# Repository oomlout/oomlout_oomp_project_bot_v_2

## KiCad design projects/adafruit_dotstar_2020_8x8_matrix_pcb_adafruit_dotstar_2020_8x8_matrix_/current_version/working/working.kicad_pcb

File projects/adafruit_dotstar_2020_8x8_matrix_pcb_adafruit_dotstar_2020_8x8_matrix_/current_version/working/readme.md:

# dotstar_2020_8x8_matrix_pcb
 
## summary 
* id: adafruit_dotstar_2020_8x8_matrix_pcb_adafruit_dotstar_2020_8x8_matrix_
* user: adafruit
* name: dotstar_2020_8x8_matrix_pcb
* board: adafruit_dotstar_2020_8x8_matrix_
* repo: https://github.com/adafruit/DotStar-2020-8x8-Matrix-PCB

* src_file_repo_sch: 
* src_file_repo_sch_link: https://github.com/adafruit/DotStar-2020-8x8-Matrix-PCB/tree/master/
* full details link: https://github.com/oomlout/oomlout_oomp_project_bot_v_2/tree/main/projects/adafruit_dotstar_2020_8x8_matrix_pcb_adafruit_dotstar_2020_8x8_matrix_/current_version/working  

## schematic  
  
[schematic (pdf)](working_schematic.pdf) 

## pcb  

[board (pdf)](working.pdf)  

## working_bom
| Id | Designator | Footprint | Quantity | Designation | Supplier and ref |  | None | 
| --- | --- | --- | --- | --- | --- | --- | --- | 
| 1 | LED61,LED15,LED52,LED5,LED2,LED56,LED29,LED42,LED31,LED59,LED53,LED34,LED33,LED37,LED30,LED3,LED13,LED58,LED16,LED47,LED54,LED48,LED6,LED27,LED62,LED21,LED20,LED49,LED10,LED8,LED32,LED22,LED45,LED55,LED40,LED23,LED36,LED35,LED4,LED26,LED7,LED18,LED43,LED12,LED19,LED60,LED63,LED9,LED11,LED46,LED50,LED28,LED38,LED41,LED17,LED39,LED51,LED64,LED24,LED44,LED57,LED14,LED1,LED25 | APA102_2020 | 64 |  |  |  | [''] | 
| 2 | @HOLE10,@HOLE0,@HOLE5,@HOLE3,@HOLE8,@HOLE2,@HOLE18,@HOLE16,@HOLE4,@HOLE6,@HOLE21,@HOLE11,@HOLE19,@HOLE9,@HOLE1,@HOLE15,@HOLE17,@HOLE12,@HOLE23,@HOLE22,@HOLE20,@HOLE13,@HOLE7,@HOLE14 |  | 24 |  |  |  | [''] | 
| 3 | FID2,FID3,FID1 | FIDUCIAL_0.5MM | 3 | FIDUCIAL_0.5MM |  |  | [''] | 
| 4 | CO0,V3,G3,V2,DI0,V1,G2,DO0,CI0,G1 | TP20R | 10 | TPTP20R |  |  | [''] | 
| 5 | U$1 | ADAFRUIT_TEXT_20MM | 1 |  |  |  | [''] | 

## bom_schematic
| Ref | Qnty | Value | Cmp name | Footprint | Description | Vendor | DNP | 
| --- | --- | --- | --- | --- | --- | --- | --- | 
| CI0 | 1 | TPTP20R | TPTP20R | working:TP20R |  |  |  | 
| CO0 | 1 | TPTP20R | TPTP20R | working:TP20R |  |  |  | 
| DI0 | 1 | TPTP20R | TPTP20R | working:TP20R |  |  |  | 
| DO0 | 1 | TPTP20R | TPTP20R | working:TP20R |  |  |  | 
| FID1, FID2, FID3 | 3 | FIDUCIAL_0.5MM | FIDUCIAL_0.5MM | working:FIDUCIAL_0.5MM |  |  |  | 
| G1, G2, G3 | 3 | TPTP20R | TPTP20R | working:TP20R |  |  |  | 
| LED1, LED2, LED3, LED4, LED5, LED6, LED7, LED8, LED9, LED10, LED11, LED12, LED13, LED14, LED15, LED16, LED17, LED18, LED19, LED20, LED21, LED22, LED23, LED24, LED25, LED26, LED27, LED28, LED29, LED30, LED31, LED32, LED33, LED34, LED35, LED36, LED37, LED38, LED39, LED40, LED41, LED42, LED43, LED44, LED45, LED46, LED47, LED48, LED49, LED50, LED51, LED52, LED53, LED54, LED55, LED56, LED57, LED58, LED59, LED60, LED61, LED62, LED63, LED64 | 64 | APA1022020 | APA1022020 | working:APA102_2020 |  |  |  | 
| V1, V2, V3 | 3 | TPTP20R | TPTP20R | working:TP20R |  |  |  |

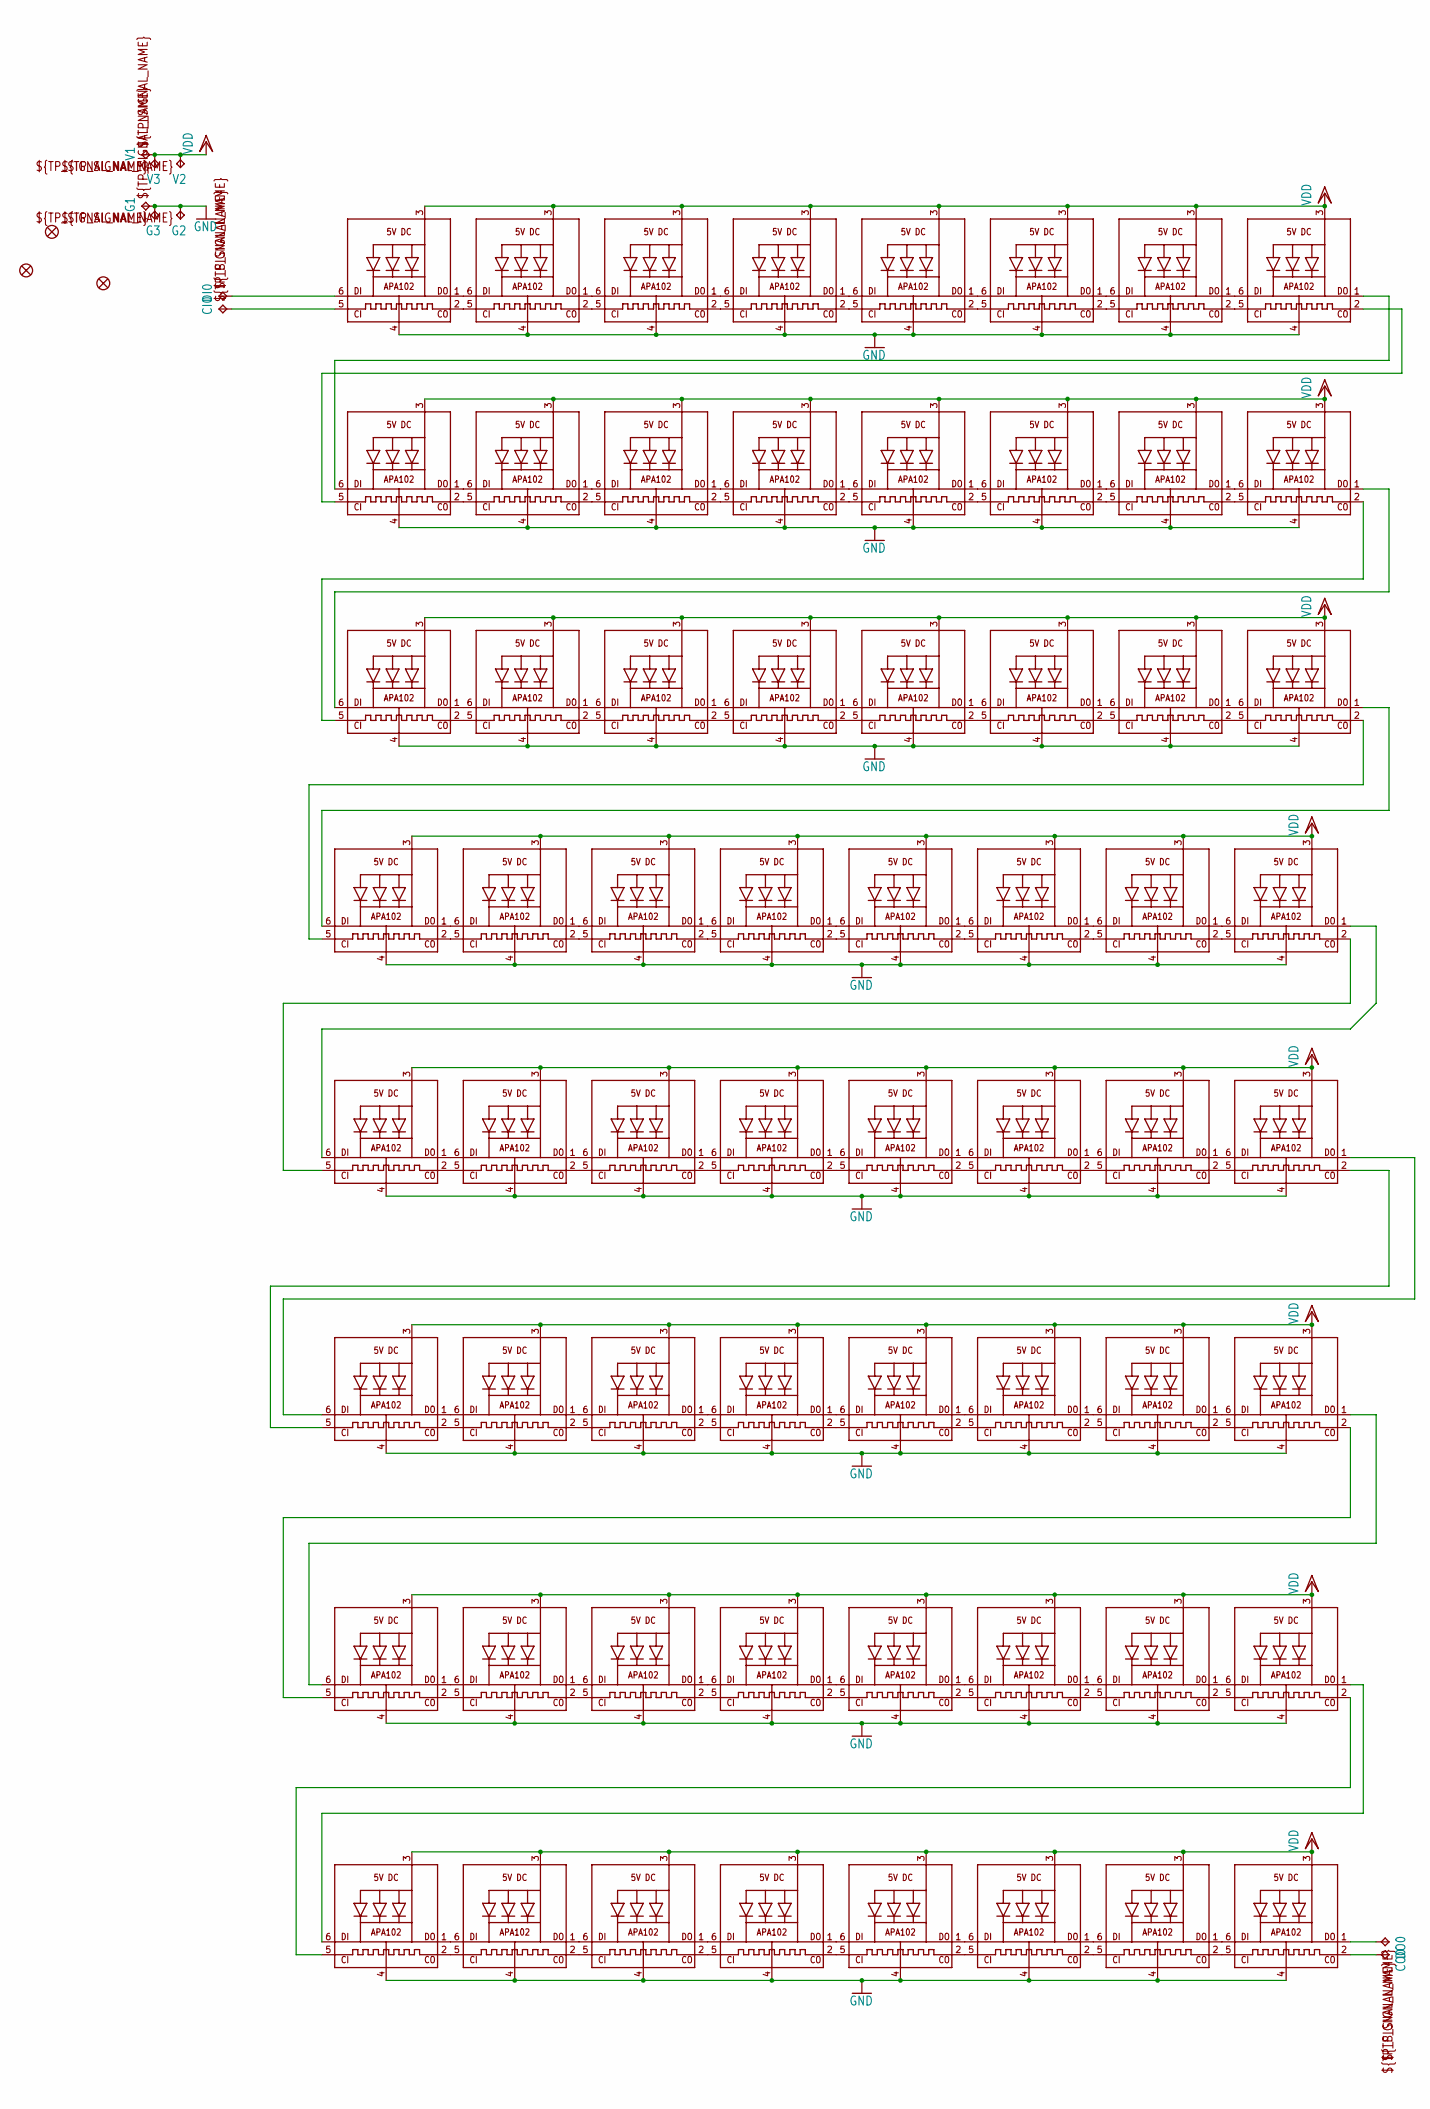
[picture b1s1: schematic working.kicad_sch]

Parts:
CI0: TPTP20R; TP20R
CO0: TPTP20R; TP20R
DI0: TPTP20R; TP20R
DO0: TPTP20R; TP20R
FID1, FID2, FID3: FIDUCIAL_0.5MM
G1, G2, G3: TPTP20R; TP20R
LED1, LED2, LED3, LED4, LED5, LED6, LED7, LED8, LED9, LED10, LED11, LED12, LED13, LED14, LED15, LED16, LED17, LED18, LED19, LED20, LED21, LED22, LED23, LED24, LED25, LED26, LED27, LED28, LED29, LED30, LED31, LED32, LED33, LED34, LED35, LED36, LED37, LED38, LED39, LED40, LED41, LED42, LED43, LED44, LED45, LED46, LED47, LED48, LED49, LED50, LED51, LED52, LED53, LED54, LED55, LED56, LED57, LED58, LED59, LED60, LED61, LED62, LED63, LED64: APA1022020; APA102_2020
V1, V2, V3: TPTP20R; TP20R

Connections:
C0: CO0.TP, LED64.2 (CKO)
CIN: CI0.TP, LED1.5 (CKI)
D0: DO0.TP, LED64.1 (DO)
DIN: DI0.TP, LED1.6 (DI)
GND: G1.TP, G2.TP, G3.TP, LED1.4 (GND), LED2.4 (GND), LED3.4 (GND), LED4.4 (GND), LED5.4 (GND), LED6.4 (GND), LED7.4 (GND), LED8.4 (GND), LED9.4 (GND), LED10.4 (GND), LED11.4 (GND), LED12.4 (GND), LED13.4 (GND), LED14.4 (GND), LED15.4 (GND), LED16.4 (GND), LED17.4 (GND), LED18.4 (GND), LED19.4 (GND), LED20.4 (GND), LED21.4 (GND), LED22.4 (GND), LED23.4 (GND), LED24.4 (GND), LED25.4 (GND), LED26.4 (GND), LED27.4 (GND), LED28.4 (GND), LED29.4 (GND), LED30.4 (GND), LED31.4 (GND), LED32.4 (GND), LED33.4 (GND), LED34.4 (GND), LED35.4 (GND), LED36.4 (GND), LED37.4 (GND), LED38.4 (GND), LED39.4 (GND), LED40.4 (GND), LED41.4 (GND), LED42.4 (GND), LED43.4 (GND), LED44.4 (GND), LED45.4 (GND), LED46.4 (GND), LED47.4 (GND), LED48.4 (GND), LED49.4 (GND), LED50.4 (GND), LED51.4 (GND), LED52.4 (GND), LED53.4 (GND), LED54.4 (GND), LED55.4 (GND), LED56.4 (GND), LED57.4 (GND), LED58.4 (GND), LED59.4 (GND), LED60.4 (GND), LED61.4 (GND), LED62.4 (GND), LED63.4 (GND), LED64.4 (GND)
unnamed: LED1.1 (DO), LED2.6 (DI)
unnamed: LED1.2 (CKO), LED2.5 (CKI)
unnamed: LED2.1 (DO), LED3.6 (DI)
unnamed: LED2.2 (CKO), LED3.5 (CKI)
unnamed: LED3.1 (DO), LED4.6 (DI)
unnamed: LED3.2 (CKO), LED4.5 (CKI)
unnamed: LED4.1 (DO), LED5.6 (DI)
unnamed: LED4.2 (CKO), LED5.5 (CKI)
unnamed: LED5.1 (DO), LED6.6 (DI)
unnamed: LED5.2 (CKO), LED6.5 (CKI)
unnamed: LED6.1 (DO), LED7.6 (DI)
unnamed: LED6.2 (CKO), LED7.5 (CKI)
unnamed: LED7.1 (DO), LED8.6 (DI)
unnamed: LED7.2 (CKO), LED8.5 (CKI)
unnamed: LED9.1 (DO), LED10.6 (DI)
unnamed: LED9.2 (CKO), LED10.5 (CKI)
unnamed: LED10.1 (DO), LED11.6 (DI)
unnamed: LED10.2 (CKO), LED11.5 (CKI)
unnamed: LED11.1 (DO), LED12.6 (DI)
unnamed: LED11.2 (CKO), LED12.5 (CKI)
unnamed: LED12.1 (DO), LED13.6 (DI)
unnamed: LED12.2 (CKO), LED13.5 (CKI)
unnamed: LED13.1 (DO), LED14.6 (DI)
unnamed: LED13.2 (CKO), LED14.5 (CKI)
unnamed: LED14.1 (DO), LED15.6 (DI)
unnamed: LED14.2 (CKO), LED15.5 (CKI)
unnamed: LED15.1 (DO), LED16.6 (DI)
unnamed: LED15.2 (CKO), LED16.5 (CKI)
unnamed: LED17.1 (DO), LED18.6 (DI)
unnamed: LED17.2 (CKO), LED18.5 (CKI)
unnamed: LED18.1 (DO), LED19.6 (DI)
unnamed: LED18.2 (CKO), LED19.5 (CKI)
unnamed: LED19.1 (DO), LED20.6 (DI)
unnamed: LED19.2 (CKO), LED20.5 (CKI)
unnamed: LED20.1 (DO), LED21.6 (DI)
unnamed: LED20.2 (CKO), LED21.5 (CKI)
unnamed: LED21.1 (DO), LED22.6 (DI)
unnamed: LED21.2 (CKO), LED22.5 (CKI)
unnamed: LED22.1 (DO), LED23.6 (DI)
unnamed: LED22.2 (CKO), LED23.5 (CKI)
unnamed: LED23.1 (DO), LED24.6 (DI)
unnamed: LED23.2 (CKO), LED24.5 (CKI)
unnamed: LED25.1 (DO), LED26.6 (DI)
unnamed: LED25.2 (CKO), LED26.5 (CKI)
unnamed: LED26.1 (DO), LED27.6 (DI)
unnamed: LED26.2 (CKO), LED27.5 (CKI)
unnamed: LED27.1 (DO), LED28.6 (DI)
unnamed: LED27.2 (CKO), LED28.5 (CKI)
unnamed: LED28.1 (DO), LED29.6 (DI)
unnamed: LED28.2 (CKO), LED29.5 (CKI)
unnamed: LED29.1 (DO), LED30.6 (DI)
unnamed: LED29.2 (CKO), LED30.5 (CKI)
unnamed: LED30.1 (DO), LED31.6 (DI)
unnamed: LED30.2 (CKO), LED31.5 (CKI)
unnamed: LED31.1 (DO), LED32.6 (DI)
unnamed: LED31.2 (CKO), LED32.5 (CKI)
unnamed: LED33.1 (DO), LED34.6 (DI)
unnamed: LED33.2 (CKO), LED34.5 (CKI)
unnamed: LED34.1 (DO), LED35.6 (DI)
unnamed: LED34.2 (CKO), LED35.5 (CKI)
unnamed: LED35.1 (DO), LED36.6 (DI)
unnamed: LED35.2 (CKO), LED36.5 (CKI)
unnamed: LED36.1 (DO), LED37.6 (DI)
unnamed: LED36.2 (CKO), LED37.5 (CKI)
unnamed: LED37.1 (DO), LED38.6 (DI)
unnamed: LED37.2 (CKO), LED38.5 (CKI)
unnamed: LED38.1 (DO), LED39.6 (DI)
unnamed: LED38.2 (CKO), LED39.5 (CKI)
unnamed: LED39.1 (DO), LED40.6 (DI)
unnamed: LED39.2 (CKO), LED40.5 (CKI)
unnamed: LED41.1 (DO), LED42.6 (DI)
unnamed: LED41.2 (CKO), LED42.5 (CKI)
unnamed: LED42.1 (DO), LED43.6 (DI)
unnamed: LED42.2 (CKO), LED43.5 (CKI)
unnamed: LED43.1 (DO), LED44.6 (DI)
unnamed: LED43.2 (CKO), LED44.5 (CKI)
unnamed: LED44.1 (DO), LED45.6 (DI)
unnamed: LED44.2 (CKO), LED45.5 (CKI)
unnamed: LED45.1 (DO), LED46.6 (DI)
unnamed: LED45.2 (CKO), LED46.5 (CKI)
unnamed: LED46.1 (DO), LED47.6 (DI)
unnamed: LED46.2 (CKO), LED47.5 (CKI)
unnamed: LED47.1 (DO), LED48.6 (DI)
unnamed: LED47.2 (CKO), LED48.5 (CKI)
unnamed: LED49.1 (DO), LED50.6 (DI)
unnamed: LED49.2 (CKO), LED50.5 (CKI)
unnamed: LED50.1 (DO), LED51.6 (DI)
unnamed: LED50.2 (CKO), LED51.5 (CKI)
unnamed: LED51.1 (DO), LED52.6 (DI)
unnamed: LED51.2 (CKO), LED52.5 (CKI)
unnamed: LED52.1 (DO), LED53.6 (DI)
unnamed: LED52.2 (CKO), LED53.5 (CKI)
unnamed: LED53.1 (DO), LED54.6 (DI)
unnamed: LED53.2 (CKO), LED54.5 (CKI)
unnamed: LED54.1 (DO), LED55.6 (DI)
unnamed: LED54.2 (CKO), LED55.5 (CKI)
unnamed: LED55.1 (DO), LED56.6 (DI)
unnamed: LED55.2 (CKO), LED56.5 (CKI)
unnamed: LED57.1 (DO), LED58.6 (DI)
unnamed: LED57.2 (CKO), LED58.5 (CKI)
unnamed: LED58.1 (DO), LED59.6 (DI)
unnamed: LED58.2 (CKO), LED59.5 (CKI)
unnamed: LED59.1 (DO), LED60.6 (DI)
unnamed: LED59.2 (CKO), LED60.5 (CKI)
unnamed: LED60.1 (DO), LED61.6 (DI)
unnamed: LED60.2 (CKO), LED61.5 (CKI)
unnamed: LED61.1 (DO), LED62.6 (DI)
unnamed: LED61.2 (CKO), LED62.5 (CKI)
unnamed: LED62.1 (DO), LED63.6 (DI)
unnamed: LED62.2 (CKO), LED63.5 (CKI)
unnamed: LED63.1 (DO), LED64.6 (DI)
unnamed: LED63.2 (CKO), LED64.5 (CKI)
unnamed: LED8.1 (DO), LED9.6 (DI)
unnamed: LED8.2 (CKO), LED9.5 (CKI)
unnamed: LED16.1 (DO), LED17.6 (DI)
unnamed: LED16.2 (CKO), LED17.5 (CKI)
unnamed: LED24.1 (DO), LED25.6 (DI)
unnamed: LED24.2 (CKO), LED25.5 (CKI)
unnamed: LED32.1 (DO), LED33.6 (DI)
unnamed: LED32.2 (CKO), LED33.5 (CKI)
unnamed: LED56.1 (DO), LED57.6 (DI)
unnamed: LED56.2 (CKO), LED57.5 (CKI)
unnamed: LED48.2 (CKO), LED49.5 (CKI)
unnamed: LED48.1 (DO), LED49.6 (DI)
unnamed: LED40.2 (CKO), LED41.5 (CKI)
unnamed: LED40.1 (DO), LED41.6 (DI)
VDD: LED1.3 (VDD), LED2.3 (VDD), LED3.3 (VDD), LED4.3 (VDD), LED5.3 (VDD), LED6.3 (VDD), LED7.3 (VDD), LED8.3 (VDD), LED9.3 (VDD), LED10.3 (VDD), LED11.3 (VDD), LED12.3 (VDD), LED13.3 (VDD), LED14.3 (VDD), LED15.3 (VDD), LED16.3 (VDD), LED17.3 (VDD), LED18.3 (VDD), LED19.3 (VDD), LED20.3 (VDD), LED21.3 (VDD), LED22.3 (VDD), LED23.3 (VDD), LED24.3 (VDD), LED25.3 (VDD), LED26.3 (VDD), LED27.3 (VDD), LED28.3 (VDD), LED29.3 (VDD), LED30.3 (VDD), LED31.3 (VDD), LED32.3 (VDD), LED33.3 (VDD), LED34.3 (VDD), LED35.3 (VDD), LED36.3 (VDD), LED37.3 (VDD), LED38.3 (VDD), LED39.3 (VDD), LED40.3 (VDD), LED41.3 (VDD), LED42.3 (VDD), LED43.3 (VDD), LED44.3 (VDD), LED45.3 (VDD), LED46.3 (VDD), LED47.3 (VDD), LED48.3 (VDD), LED49.3 (VDD), LED50.3 (VDD), LED51.3 (VDD), LED52.3 (VDD), LED53.3 (VDD), LED54.3 (VDD), LED55.3 (VDD), LED56.3 (VDD), LED57.3 (VDD), LED58.3 (VDD), LED59.3 (VDD), LED60.3 (VDD), LED61.3 (VDD), LED62.3 (VDD), LED63.3 (VDD), LED64.3 (VDD), V1.TP, V2.TP, V3.TP

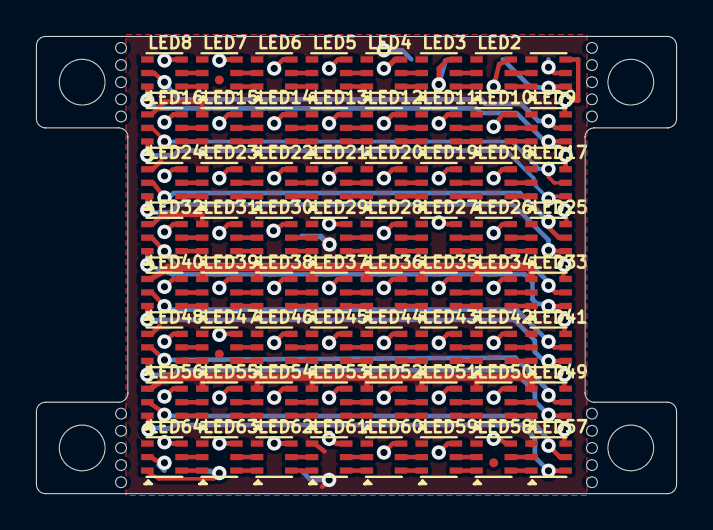
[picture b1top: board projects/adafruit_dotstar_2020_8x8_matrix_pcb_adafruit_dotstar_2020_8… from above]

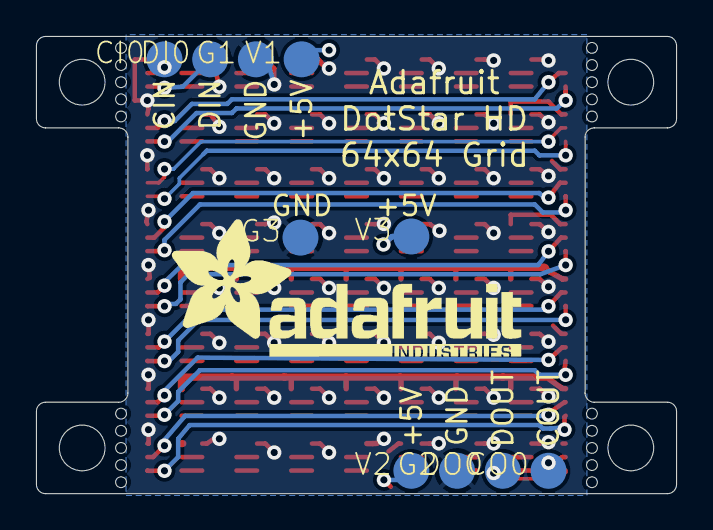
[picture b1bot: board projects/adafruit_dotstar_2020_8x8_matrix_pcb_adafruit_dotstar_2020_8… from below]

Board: 2 copper layers, 35.6 x 25.4 mm, 102 parts (11 on the bottom side), 132 nets.

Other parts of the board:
@HOLE0, @HOLE1, @HOLE2, @HOLE3, @HOLE4, @HOLE5, @HOLE6, @HOLE7, @HOLE8, @HOLE9, @HOLE10, @HOLE11, @HOLE12, @HOLE13, @HOLE14, @HOLE15, @HOLE16, @HOLE17, @HOLE18, @HOLE19, @HOLE20, @HOLE21, @HOLE22, @HOLE23: (no value)
U$1: ADAFRUIT_TEXT_20MM

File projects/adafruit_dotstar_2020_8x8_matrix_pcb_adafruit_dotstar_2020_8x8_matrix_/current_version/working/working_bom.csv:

"Id";"Designator";"Footprint";"Quantity";"Designation";"Supplier and ref";
1;"LED61,LED15,LED52,LED5,LED2,LED56,LED29,LED42,LED31,LED59,LED53,LED34,LED33,LED37,LED30,LED3,LED13,LED58,LED16,LED47,LED54,LED48,LED6,LED27,LED62,LED21,LED20,LED49,LED10,LED8,LED32,LED22,LED45,LED55,LED40,LED23,LED36,LED35,LED4,LED26,LED7,LED18,LED43,LED12,LED19,LED60,LED63,LED9,LED11,LED46,LED50,LED28,LED38,LED41,LED17,LED39,LED51,LED64,LED24,LED44,LED57,LED14,LED1,LED25";"APA102_2020";64;"";;;
2;"@HOLE10,@HOLE0,@HOLE5,@HOLE3,@HOLE8,@HOLE2,@HOLE18,@HOLE16,@HOLE4,@HOLE6,@HOLE21,@HOLE11,@HOLE19,@HOLE9,@HOLE1,@HOLE15,@HOLE17,@HOLE12,@HOLE23,@HOLE22,@HOLE20,@HOLE13,@HOLE7,@HOLE14";"";24;"";;;
3;"FID2,FID3,FID1";"FIDUCIAL_0.5MM";3;"FIDUCIAL_0.5MM";;;
4;"CO0,V3,G3,V2,DI0,V1,G2,DO0,CI0,G1";"TP20R";10;"TPTP20R";;;
5;"U$1";"ADAFRUIT_TEXT_20MM";1;"";;;

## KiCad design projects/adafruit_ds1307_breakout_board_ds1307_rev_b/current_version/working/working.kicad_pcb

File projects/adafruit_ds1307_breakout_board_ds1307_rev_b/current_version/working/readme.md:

# ds1307_breakout_board
 
## summary 
* id: adafruit_ds1307_breakout_board_ds1307_rev_b
* user: adafruit
* name: ds1307_breakout_board
* board: ds1307_rev_b
* repo: https://github.com/adafruit/DS1307-breakout-board

* src_file_repo_sch: 
* src_file_repo_sch_link: https://github.com/adafruit/DS1307-breakout-board/tree/master/
* full details link: https://github.com/oomlout/oomlout_oomp_project_bot_v_2/tree/main/projects/adafruit_ds1307_breakout_board_ds1307_rev_b/current_version/working  

## schematic  
  
[schematic (pdf)](working_schematic.pdf) 

## pcb  

[board (pdf)](working.pdf)  

## working_bom
| Id | Designator | Footprint | Quantity | Designation | Supplier and ref |  | None | 
| --- | --- | --- | --- | --- | --- | --- | --- | 
| 1 | U$1,U$4 | MOUNTINGHOLE_2.0_PLATED | 2 | MOUNTINGHOLE2.0 |  |  | [''] | 
| 2 | U1 | SOIC8_150MIL | 1 | DS1307 |  |  | [''] | 
| 3 | Q1 | CRYSTAL_8X3.8 | 1 | 32.768 |  |  | [''] | 
| 4 | R2,R1 | 0805-NO | 2 | 10K |  |  | [''] | 
| 5 | JP2 | 1X05_ROUND_76 | 1 |  |  |  | [''] | 
| 6 | FID1,FID2 | FIDUCIAL_1MM | 2 | FIDUCIAL" |  |  | [''] | 
| 7 | U$2 | ADAFRUIT_3.5MM | 1 |  |  |  | [''] | 
| 8 | C1 | 0805-NO | 1 | 0.1uF |  |  | [''] | 
| 9 | B1 | CR1220 | 1 | CR1220 |  |  | [''] | 
| 10 | SJ1,SJ2 | SOLDERJUMPER_CLOSEDWIRE | 2 |  |  |  | [''] | 
| 11 | U$3 | PCBFEAT-REV-040 | 1 |  |  |  | [''] | 
| 12 | U$5 | ADAFRUIT_5MM | 1 |  |  |  | [''] | 

## bom_schematic
| Ref | Qnty | Value | Cmp name | Footprint | Description | Vendor | DNP | 
| --- | --- | --- | --- | --- | --- | --- | --- | 
| B1 | 1 | CR1220 | BATTERYCR1220_SMT | working:CR1220 |  |  |  | 
| C1 | 1 | 0.1uF | CAP_CERAMIC0805-NOOUTLINE | working:0805-NO |  |  |  | 
| FID1, FID2 | 2 | FIDUCIAL"" | FIDUCIAL{dblquote}{dblquote} | working:FIDUCIAL_1MM |  |  |  | 
| JP2 | 1 | HEADER-1X576MIL | HEADER-1X576MIL | working:1X05_ROUND_76 |  |  |  | 
| Q1 | 1 | 32.768 | CRYSTAL8.0X3.8 | working:CRYSTAL_8X3.8 |  |  |  | 
| R1, R2 | 2 | 10K | RESISTOR0805_NOOUTLINE | working:0805-NO |  |  |  | 
| SJ1, SJ2 | 2 | SOLDERJUMPER_CLOSED | SOLDERJUMPER_CLOSED | working:SOLDERJUMPER_CLOSEDWIRE |  |  |  | 
| U1 | 1 | DS1307 | RTC_DS1307 | working:SOIC8_150MIL |  |  |  | 
| U$1, U$4 | 2 | MOUNTINGHOLE2.0 | MOUNTINGHOLE2.0 | working:MOUNTINGHOLE_2.0_PLATED |  |  |  | 

## mounting_holes
| x | y | package | value | ref | size | 
| --- | --- | --- | --- | --- | --- | 
| 0.0 | 20.32 | MOUNTINGHOLE_2.0_PLATED | MOUNTINGHOLE2.0 | U$1 | m3 | 
| 16.51 | 0.0 | MOUNTINGHOLE_2.0_PLATED | MOUNTINGHOLE2.0 | U$4 | m3 |

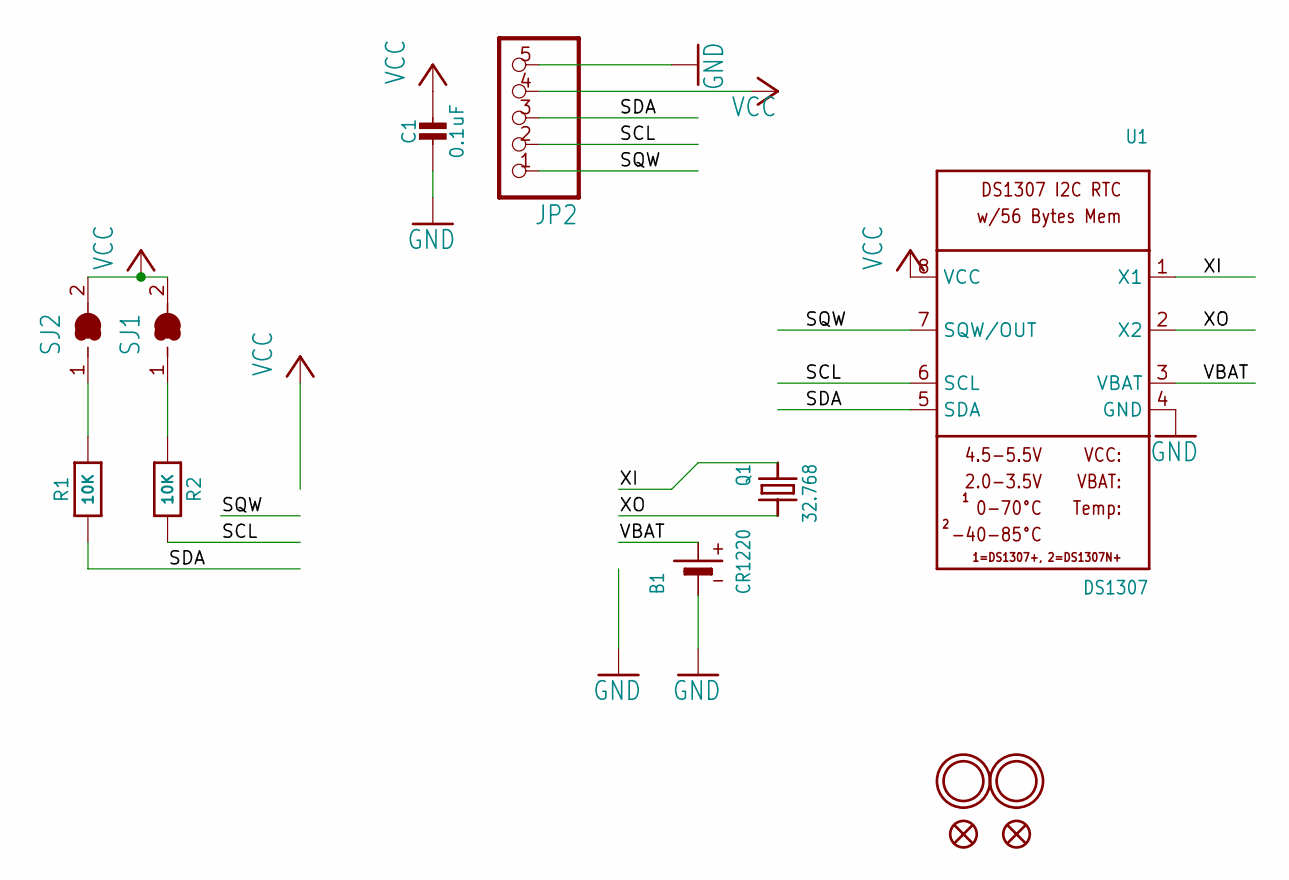
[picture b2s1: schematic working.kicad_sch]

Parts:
B1: CR1220
C1: 0.1uF; 0805-NO
FID1, FID2: FIDUCIAL""; FIDUCIAL_1MM
JP2: HEADER-1X576MIL; 1X05_ROUND_76
Q1: 32.768; CRYSTAL_8X3.8
R1, R2: 10K; 0805-NO
SJ1, SJ2: SOLDERJUMPER_CLOSED; SOLDERJUMPER_CLOSEDWIRE
U1: DS1307; SOIC8_150MIL
U$1, U$4: MOUNTINGHOLE2.0; MOUNTINGHOLE_2.0_PLATED

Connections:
GND: B1.-, C1.2, JP2.5, U1.4 (GND)
unnamed: R2.1, SJ1.1
unnamed: R1.2, SJ2.1
SCL: JP2.2, R2.2, U1.6 (SCL)
SDA: JP2.3, R1.1, U1.5 (SDA)
SQW: JP2.1, U1.7 (SQW/OUT)
VBAT: B1.+$1 (+), U1.3 (VBAT)
VCC: C1.1, JP2.4, SJ1.2, SJ2.2, U1.8 (VCC)
XI: Q1.P$1 (1), U1.1 (X1)
XO: Q1.P$4 (2), U1.2 (X2)

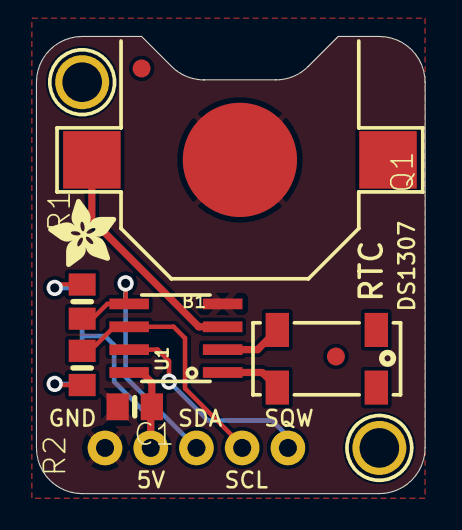
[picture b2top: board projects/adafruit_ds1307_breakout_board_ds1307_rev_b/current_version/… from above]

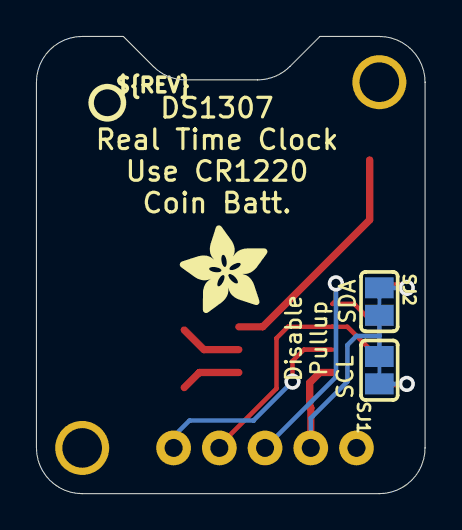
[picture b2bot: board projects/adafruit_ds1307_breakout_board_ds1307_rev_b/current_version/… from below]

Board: 16 copper layers, 21.6 x 25.4 mm, 16 parts (4 on the bottom side), 10 nets.

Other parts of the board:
U$2: ADAFRUIT_3.5MM
U$3: PCBFEAT-REV-040
U$5: ADAFRUIT_5MM

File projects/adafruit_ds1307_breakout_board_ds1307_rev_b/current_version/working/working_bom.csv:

"Id";"Designator";"Footprint";"Quantity";"Designation";"Supplier and ref";
1;"U$1,U$4";"MOUNTINGHOLE_2.0_PLATED";2;"MOUNTINGHOLE2.0";;;
2;"U1";"SOIC8_150MIL";1;"DS1307";;;
3;"Q1";"CRYSTAL_8X3.8";1;"32.768";;;
4;"R2,R1";"0805-NO";2;"10K";;;
5;"JP2";"1X05_ROUND_76";1;"";;;
6;"FID1,FID2";"FIDUCIAL_1MM";2;"FIDUCIAL""";;;
7;"U$2";"ADAFRUIT_3.5MM";1;"";;;
8;"C1";"0805-NO";1;"0.1uF";;;
9;"B1";"CR1220";1;"CR1220";;;
10;"SJ1,SJ2";"SOLDERJUMPER_CLOSEDWIRE";2;"";;;
11;"U$3";"PCBFEAT-REV-040";1;"";;;
12;"U$5";"ADAFRUIT_5MM";1;"";;;

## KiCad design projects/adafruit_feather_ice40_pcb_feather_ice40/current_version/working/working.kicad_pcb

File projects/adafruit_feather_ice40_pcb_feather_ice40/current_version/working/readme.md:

# feather_ice40_pcb
 
## summary 
* id: adafruit_feather_ice40_pcb_feather_ice40
* user: adafruit
* name: feather_ice40_pcb
* board: feather_ice40
* repo: https://github.com/adafruit/Feather-ICE40-PCB
* src_file_repo_kicad_pcb: feather_ice40.kicad_pcb
* src_file_repo_kicad_pcb_link: https://github.com/adafruit/Feather-ICE40-PCB/tree/master/feather_ice40.kicad_pcb

* src_file_repo_sch: feather_ice40.sch
* src_file_repo_sch_link: https://github.com/adafruit/Feather-ICE40-PCB/tree/master/feather_ice40.sch
* full details link: https://github.com/oomlout/oomlout_oomp_project_bot_v_2/tree/main/projects/adafruit_feather_ice40_pcb_feather_ice40/current_version/working  

## schematic  
  
[schematic (pdf)](working_schematic.pdf) 

## pcb  

[board (pdf)](working.pdf)  

## working_bom
| Id | Designator | Footprint | Quantity | Designation | Supplier and ref |  | None | 
| --- | --- | --- | --- | --- | --- | --- | --- | 
| 1 | U5 | QFN-32-1EP_5x5mm_Pitch0.5mm | 1 | SAMD21E |  |  | [''] | 
| 2 | D1 | D_SOD-123 | 1 | MBR120 |  |  | [''] | 
| 3 | J2 | JST_PH_S2B-PH-SM4-TB_02x2.00mm_Angled | 1 | CONN_01X02 |  |  | [''] | 
| 4 | J1 | Mini-USB-B-OshPark | 1 | USB_OTG |  |  | [''] | 
| 5 | J6,J5,J4,J3 | MountingHole_2.7mm_M2.5 | 4 | CONN_01X01 |  |  | [''] | 
| 6 | R8,R5,R10 | R_0603 | 3 | 1k |  |  | [''] | 
| 7 | R4 | R_0603 | 1 | 100k |  |  | [''] | 
| 8 | C20,C19,C16,C14,C6 | C_0603 | 5 | 10uF |  |  | [''] | 
| 9 | C18,C7 | C_0603 | 2 | 1uF |  |  | [''] | 
| 10 | D2 | D_0603 | 1 | Yellow |  |  | [''] | 
| 11 | D3 | D_0603 | 1 | Red |  |  | [''] | 
| 12 | U6 | SOT-23-5 | 1 | MCP73831 |  |  | [''] | 
| 13 | U4 | SOT-23-5 | 1 | SPX3819M5-L-1-2/TR |  |  | [''] | 
| 14 | U3 | SOT-23-5 | 1 | SPX3819M5-L-3-3/TR |  |  | [''] | 
| 15 | R9 | R_0805 | 1 | 10k |  |  | [''] | 
| 16 | J9 | Pin_Header_Straight_1x16_Pitch2.54mm | 1 | FeatherBottom |  |  | [''] | 
| 17 | J10 | Pin_Header_Straight_1x12_Pitch2.54mm | 1 | FeatherTop |  |  | [''] | 
| 18 | R2 | R_0603 | 1 | 100 |  |  | [''] | 
| 19 | R1,R3 | R_0603 | 2 | 10k |  |  | [''] | 
| 20 | U1 | QFN-48-1EP_7x7mm_Pitch0.5mm | 1 | ICE40UP5K-SG48 |  |  | [''] | 
| 21 | C8,C5,C4,C2,C1 | C_0603 | 5 | 0.1uF |  |  | [''] | 
| 22 | R7,R6 | R_0603 | 2 | 4.7k |  |  | [''] | 
| 23 | U2 | SOIC-8_3.9x4.9mm_Pitch1.27mm | 1 | IS25LPXXX |  |  | [''] | 
| 24 | J8 | Pin_Header_Straight_1x04_Pitch2.54mm | 1 | Conn_01x04 |  |  | [''] | 
| 25 | D4 | LED_WS2812B-PLCC4 | 1 | Neopixel_THT |  |  | [''] | 
| 26 | SW1 | SW_SPST_KMR2 | 1 | SW_SPST |  |  | [''] | 
| 27 | J7 | Pin_Header_Straight_2x05_Pitch1.27mm_SMD | 1 | CONN_02X05 |  |  | [''] | 

## bom_schematic
no data

## mounting_holes
| x | y | package | value | ref | size | 
| --- | --- | --- | --- | --- | --- | 
| 45.72 | 0.0 | MountingHole_2.7mm_M2.5 | CONN_01X01 | J3 | m3 | 
| 45.72 | 17.78 | MountingHole_2.7mm_M2.5 | CONN_01X01 | J4 | m3 | 
| 0.0 | 0.0 | MountingHole_2.7mm_M2.5 | CONN_01X01 | J5 | m3 | 
| 0.0 | 17.78 | MountingHole_2.7mm_M2.5 | CONN_01X01 | J6 | m3 |

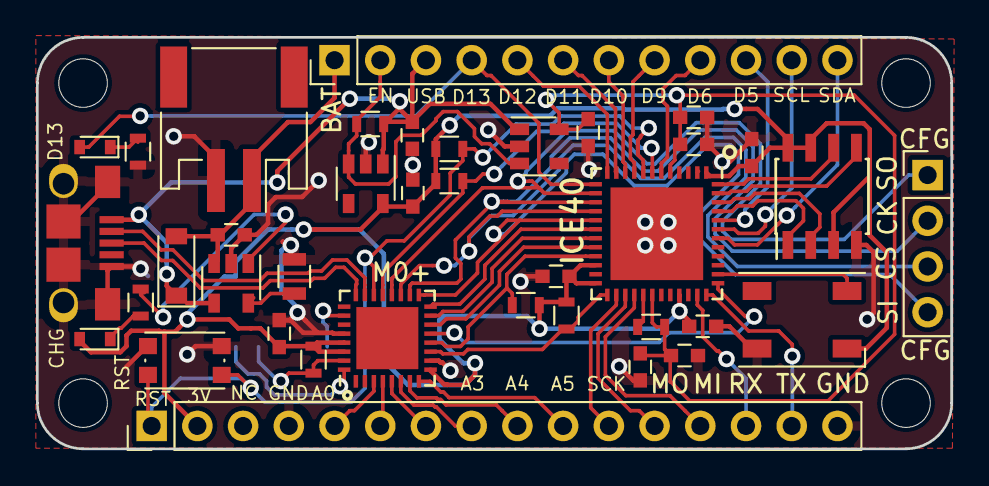
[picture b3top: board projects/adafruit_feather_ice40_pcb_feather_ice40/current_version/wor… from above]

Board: 2 copper layers, 50.8 x 22.9 mm, 43 parts (1 on the bottom side), 53 nets.

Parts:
C1, C2, C4, C5, C8: 0.1uF; C_0603
C6, C14, C16, C19, C20: 10uF; C_0603
C7, C18: 1uF; C_0603
D1: MBR120; D_SOD-123
D2: Yellow; D_0603
D3: Red; D_0603
D4: Neopixel_THT; LED_WS2812B-PLCC4
J1: USB_OTG; Mini-USB-B-OshPark
J2: CONN_01X02; JST_PH_S2B-PH-SM4-TB_02x2.00mm_Angled
J3, J4, J5, J6: CONN_01X01; MountingHole_2.7mm_M2.5
J7: CONN_02X05; Pin_Header_Straight_2x05_Pitch1.27mm_SMD
J8: Conn_01x04; Pin_Header_Straight_1x04_Pitch2.54mm
J9: FeatherBottom; Pin_Header_Straight_1x16_Pitch2.54mm
J10: FeatherTop; Pin_Header_Straight_1x12_Pitch2.54mm
R1, R3: 10k; R_0603
R2: 100; R_0603
R4: 100k; R_0603
R5, R8, R10: 1k; R_0603
R6, R7: 4.7k; R_0603
R9: 10k; R_0805
SW1: SW_SPST; SW_SPST_KMR2
U1: ICE40UP5K-SG48; QFN-48-1EP_7x7mm_Pitch0.5mm
U2: IS25LPXXX; SOIC-8_3.9x4.9mm_Pitch1.27mm
U3: SPX3819M5-L-3-3/TR; SOT-23-5
U4: SPX3819M5-L-1-2/TR; SOT-23-5
U5: SAMD21E; QFN-32-1EP_5x5mm_Pitch0.5mm
U6: MCP73831; SOT-23-5

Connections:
+1V2: C5.1, C6.1, C7.1, C8.1, C16.1, R2.1, U1.5, U1.30, U4.5
+3V3: C1.1, C2.1, C4.1, C14.1, C18.2, D2.2, D4.3, J7.1, J9.2, R1.1, R3.1, R6.1, R7.1, R10.1, U1.1, U1.22, U1.24, U1.33, U2.3, U2.7, U2.8, U3.5, U5.9, U5.29, U5.30
+5V: C19.1, D1.1, J1.1, J10.3, R4.1, U3.1, U4.1, U6.4
+BATT: C20.1, D1.2, J2.1, J10.1, U6.3
/A0: J9.5, U5.3
/A1: J9.6, U5.4
/A2: J9.7, U5.5
/A3: J9.8, U5.6
/A4: J9.9, U5.7
/A5: J9.10, U5.8
/CHARGE: R5.2, U6.1
/D5: J10.10, U1.44
/D6: J10.9, U1.6
/D9: J10.8, U1.9
/D10: J10.7, U1.10
/D11: J10.6, U1.11
/D12: J10.5, U1.12
/D13: D3.2, J10.4, U1.13
/EN: J10.2, R4.2, U3.3, U4.3
/GCLK4: U1.37, U5.13
/GCLK5: U1.20, U5.14
/M0RX: U1.18, U5.16
/M0TX: U1.19, U5.15
/M0_RST: J7.10, U5.26
/M0_SWCLK: J7.4, R10.2, U5.31
/M0_SWDIO: J7.2, U5.32
/NEOPIX: D4.4, U1.38
/USB_D+: J1.3, U5.24
/USB_D-: J1.2, U5.23
/cdone: R3.2, U1.7, U5.21
/configMISO: J8.1, U1.14, U5.20
/configMOSI: J8.4, U1.17, U5.17
/configSCK: J8.2, U1.15, U5.18
/configSS: J8.3, U1.16, U5.19
/flashMISO: U1.46, U2.2
/flashMOSI: U1.47, U2.5
/flashSCK: U1.48, U2.6
/flashSS: U1.45, U2.1
/iceMISO: J9.13, U1.28
/iceMOSI: J9.12, U1.27
/iceRX: J9.14, U1.35
/iceReset: J9.1, R1.2, SW1.2, U1.8, U5.22
/iceSCK: J9.11, U1.26
/iceSCL: J10.11, U1.43
/iceSDA: J10.12, U1.42
/iceTX: J9.15, U1.36
/sharedSCL: R6.2, U1.21, U5.12
/sharedSDA: R7.2, U1.25, U5.11
GND: C1.2, C2.2, C4.2, C5.2, C6.2, C7.2, C8.2, C14.2, C16.2, C18.1, C19.2, C20.2, D4.2, J1.5, J1.6, J2.2, J7.3, J7.5, J9.4, J9.16, R8.2, R9.2, SW1.1, U1.49, U2.4, U3.2, U4.2, U5.10, U5.28, U6.2
unnamed: D2.1, R5.1
unnamed: D3.1, R8.1
unnamed: R2.2, U1.29
unnamed: R9.1, U6.5

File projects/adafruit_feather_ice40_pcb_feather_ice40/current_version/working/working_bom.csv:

"Id";"Designator";"Footprint";"Quantity";"Designation";"Supplier and ref";
1;"U5";"QFN-32-1EP_5x5mm_Pitch0.5mm";1;"SAMD21E";;;
2;"D1";"D_SOD-123";1;"MBR120";;;
3;"J2";"JST_PH_S2B-PH-SM4-TB_02x2.00mm_Angled";1;"CONN_01X02";;;
4;"J1";"Mini-USB-B-OshPark";1;"USB_OTG";;;
5;"J6,J5,J4,J3";"MountingHole_2.7mm_M2.5";4;"CONN_01X01";;;
6;"R8,R5,R10";"R_0603";3;"1k";;;
7;"R4";"R_0603";1;"100k";;;
8;"C20,C19,C16,C14,C6";"C_0603";5;"10uF";;;
9;"C18,C7";"C_0603";2;"1uF";;;
10;"D2";"D_0603";1;"Yellow";;;
11;"D3";"D_0603";1;"Red";;;
12;"U6";"SOT-23-5";1;"MCP73831";;;
13;"U4";"SOT-23-5";1;"SPX3819M5-L-1-2/TR";;;
14;"U3";"SOT-23-5";1;"SPX3819M5-L-3-3/TR";;;
15;"R9";"R_0805";1;"10k";;;
16;"J9";"Pin_Header_Straight_1x16_Pitch2.54mm";1;"FeatherBottom";;;
17;"J10";"Pin_Header_Straight_1x12_Pitch2.54mm";1;"FeatherTop";;;
18;"R2";"R_0603";1;"100";;;
19;"R1,R3";"R_0603";2;"10k";;;
20;"U1";"QFN-48-1EP_7x7mm_Pitch0.5mm";1;"ICE40UP5K-SG48";;;
21;"C8,C5,C4,C2,C1";"C_0603";5;"0.1uF";;;
22;"R7,R6";"R_0603";2;"4.7k";;;
23;"U2";"SOIC-8_3.9x4.9mm_Pitch1.27mm";1;"IS25LPXXX";;;
24;"J8";"Pin_Header_Straight_1x04_Pitch2.54mm";1;"Conn_01x04";;;
25;"D4";"LED_WS2812B-PLCC4";1;"Neopixel_THT";;;
26;"SW1";"SW_SPST_KMR2";1;"SW_SPST";;;
27;"J7";"Pin_Header_Straight_2x05_Pitch1.27mm_SMD";1;"CONN_02X05";;;

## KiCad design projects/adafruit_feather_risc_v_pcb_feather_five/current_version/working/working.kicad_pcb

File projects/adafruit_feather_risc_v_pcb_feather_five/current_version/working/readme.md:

# feather_risc_v_pcb
 
## summary 
* id: adafruit_feather_risc_v_pcb_feather_five
* user: adafruit
* name: feather_risc_v_pcb
* board: feather_five
* repo: https://github.com/adafruit/Feather-RISC-V-PCB
* src_file_repo_kicad_pcb: feather_five.kicad_pcb
* src_file_repo_kicad_pcb_link: https://github.com/adafruit/Feather-RISC-V-PCB/tree/master/feather_five.kicad_pcb

* src_file_repo_sch: feather_five.sch
* src_file_repo_sch_link: https://github.com/adafruit/Feather-RISC-V-PCB/tree/master/feather_five.sch
* full details link: https://github.com/oomlout/oomlout_oomp_project_bot_v_2/tree/main/projects/adafruit_feather_risc_v_pcb_feather_five/current_version/working  

## schematic  
  
[schematic (pdf)](working_schematic.pdf) 

## pcb  

[board (pdf)](working.pdf)  

## working_bom
| Id | Designator | Footprint | Quantity | Designation | Supplier and ref |  | None | 
| --- | --- | --- | --- | --- | --- | --- | --- | 
| 1 | U1 | QFN-48-1EP_7x7mm_Pitch0.5mm | 1 | E310-G000 |  |  | [''] | 
| 2 | U2 | SOIC-8 | 1 | IS25LPXXX |  |  | [''] | 
| 3 | U5 | QFN-32-1EP_5x5mm_Pitch0.5mm | 1 | SAMD21E |  |  | [''] | 
| 4 | D1 | D_SOD-123 | 1 | MBR120 |  |  | [''] | 
| 5 | J2 | JST_PH_S2B-PH-SM4-TB_02x2.00mm_Angled | 1 | CONN_01X02 |  |  | [''] | 
| 6 | J1 | Mini-USB-B-OshPark | 1 | USB_OTG |  |  | [''] | 
| 7 | J6,J5,J4,J3 | MountingHole_2.7mm_M2.5 | 4 | CONN_01X01 |  |  | [''] | 
| 8 | R8,R5,R10 | R_0603 | 3 | 1k |  |  | [''] | 
| 9 | R4,R3,R2,R11 | R_0603 | 4 | 100k |  |  | [''] | 
| 10 | R1 | R_0603 | 1 | 100 |  |  | [''] | 
| 11 | Y1 | Crystal_SMD_TXC_7M-4pin_3.2x2.5mm | 1 | Crystal_GND24_Small |  |  | [''] | 
| 12 | C20,C19,C16,C14,C4 | C_0603 | 5 | 10uF |  |  | [''] | 
| 13 | C18 | C_0603 | 1 | 1uF |  |  | [''] | 
| 14 | C13,C12,C11,C10,C9,C8,C7,C6,C5 | C_0603 | 9 | .1uF |  |  | [''] | 
| 15 | C3,C2 | C_0603 | 2 | 12pF |  |  | [''] | 
| 16 | D2 | D_0603 | 1 | Yellow |  |  | [''] | 
| 17 | D3 | D_0603 | 1 | Red |  |  | [''] | 
| 18 | R7,R6 | R_0603 | 2 | 4.7k |  |  | [''] | 
| 19 | U6 | SOT-23-5 | 1 | MCP73831 |  |  | [''] | 
| 20 | U4 | SOT-23-5 | 1 | SPX3819M5-L-1-8/TR |  |  | [''] | 
| 21 | U3 | SOT-23-5 | 1 | SPX3819M5-L-3-3/TR |  |  | [''] | 
| 22 | SW1 | SW_SPST_KMR2 | 1 | SW_Push |  |  | [''] | 
| 23 | R9 | R_0805 | 1 | 10k |  |  | [''] | 
| 24 | D4 | D_SOT-23_ANK | 1 | D_Small |  |  | [''] | 
| 25 | J9 | Pin_Header_Straight_1x16_Pitch2.54mm | 1 | FeatherBottom |  |  | [''] | 
| 26 | J10 | Pin_Header_Straight_1x12_Pitch2.54mm | 1 | FeatherTop |  |  | [''] | 
| 27 | J8,J7 | Pin_Header_Straight_2x05_Pitch1.27mm_SMD | 2 | CONN_02X05 |  |  | [''] | 

## bom_schematic
no data

## mounting_holes
| x | y | package | value | ref | size | 
| --- | --- | --- | --- | --- | --- | 
| 45.72 | 0.0 | MountingHole_2.7mm_M2.5 | CONN_01X01 | J3 | m3 | 
| 45.72 | 17.78 | MountingHole_2.7mm_M2.5 | CONN_01X01 | J4 | m3 | 
| 0.0 | 0.0 | MountingHole_2.7mm_M2.5 | CONN_01X01 | J5 | m3 | 
| 0.0 | 17.78 | MountingHole_2.7mm_M2.5 | CONN_01X01 | J6 | m3 |

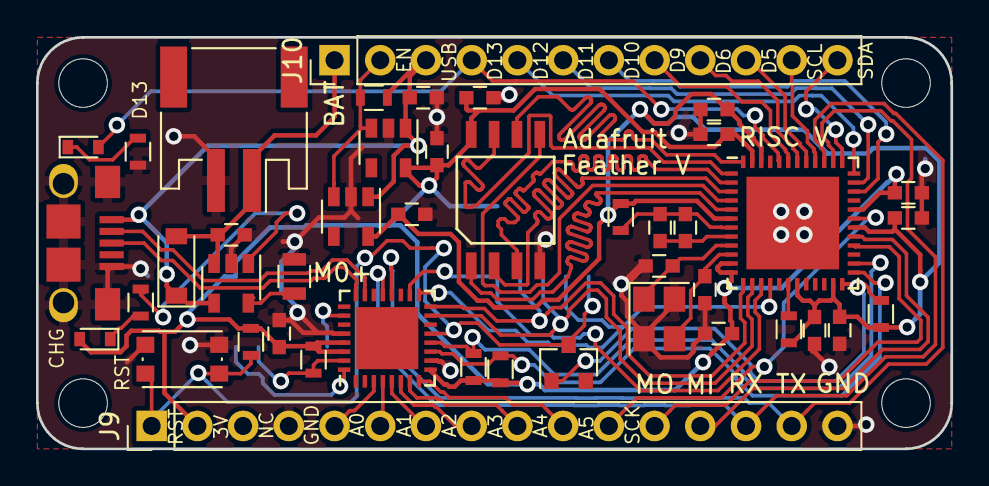
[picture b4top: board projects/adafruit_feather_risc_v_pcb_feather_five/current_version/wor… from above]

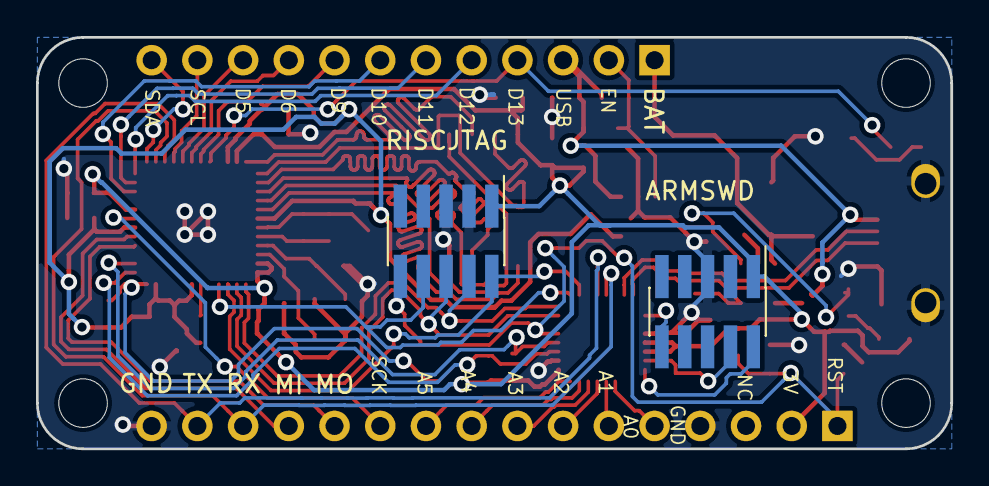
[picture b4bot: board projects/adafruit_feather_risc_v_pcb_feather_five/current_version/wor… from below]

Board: 2 copper layers, 50.8 x 22.9 mm, 50 parts (2 on the bottom side), 54 nets.

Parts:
C2, C3: 12pF; C_0603
C4, C14, C16, C19, C20: 10uF; C_0603
C5, C6, C7, C8, C9, C10, C11, C12, C13: .1uF; C_0603
C18: 1uF; C_0603
D1: MBR120; D_SOD-123
D2: Yellow; D_0603
D3: Red; D_0603
D4: D_Small; D_SOT-23_ANK
J1: USB_OTG; Mini-USB-B-OshPark
J2: CONN_01X02; JST_PH_S2B-PH-SM4-TB_02x2.00mm_Angled
J3, J4, J5, J6: CONN_01X01; MountingHole_2.7mm_M2.5
J7, J8: CONN_02X05; Pin_Header_Straight_2x05_Pitch1.27mm_SMD
J9: FeatherBottom; Pin_Header_Straight_1x16_Pitch2.54mm
J10: FeatherTop; Pin_Header_Straight_1x12_Pitch2.54mm
R1: 100; R_0603
R2, R3, R4, R11: 100k; R_0603
R5, R8, R10: 1k; R_0603
R6, R7: 4.7k; R_0603
R9: 10k; R_0805
SW1: SW_Push; SW_SPST_KMR2
U1: E310-G000; QFN-48-1EP_7x7mm_Pitch0.5mm
U2: IS25LPXXX; SOIC-8
U3: SPX3819M5-L-3-3/TR; SOT-23-5
U4: SPX3819M5-L-1-8/TR; SOT-23-5
U5: SAMD21E; QFN-32-1EP_5x5mm_Pitch0.5mm
U6: MCP73831; SOT-23-5
Y1: Crystal_GND24_Small; Crystal_SMD_TXC_7M-4pin_3.2x2.5mm

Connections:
+1V8: C4.1, C9.2, C10.2, C12.2, C16.1, R1.2, R2.2, R3.1, U1.6, U1.19, U1.23, U1.30, U1.46, U4.5
+3V3: C6.2, C8.1, C11.2, C13.1, C14.1, C18.2, D2.2, J7.1, J8.1, J9.2, R6.1, R7.1, R10.1, R11.1, U1.11, U1.12, U1.32, U1.47, U2.8, U3.5, U5.9, U5.29, U5.30
+5V: C19.1, D1.1, J1.1, J10.3, R4.1, U3.1, U4.1, U6.4
+BATT: C20.1, D1.2, J2.1, J10.1, U6.3
/A0: J9.5, U5.3
/A1: J9.6, U5.4
/A2: J9.7, U5.5
/A3: J9.8, U5.6
/A4: J9.9, U5.7
/A5: J9.10, U5.8
/CHARGE: R5.2, U6.1
/D5: J10.10, U1.41
/D6: J10.9, U1.42
/D9: J10.8, U1.43
/D10: J10.7, U1.34
/D11: J10.6, U1.35
/D12: J10.5, U1.36
/D13: D3.2, J10.4, U1.44
/EN: J10.2, R4.2, U3.3, U4.3
/FLASH_CS: U1.5, U2.1
/FLASH_IO0: U1.4, U2.5
/FLASH_IO1: U1.3, U2.2
/FLASH_IO2: U1.2, U2.3
/FLASH_IO3: U1.1, U2.7
/FLASH_SCK: U1.48, U2.6
/M0_RST: J7.10, U5.26
/M0_SWCLK: J7.4, R10.2, U5.31
/M0_SWDIO: J7.2, U5.32
/USB_D+: J1.3, U5.24
/USB_D-: J1.2, U5.23
/riscJTAG_TCK: J8.4, U1.13, U5.16
/riscJTAG_TDI: J8.8, U1.16, U5.17
/riscJTAG_TDO: J8.6, U1.14, U5.15
/riscJTAG_TMS: J8.2, U1.15, U5.18
/riscMISO: J9.13, U1.29
/riscMOSI: J9.12, U1.28
/riscRX: J9.14, U1.38, U5.21
/riscReset: D4.1, J8.10, J9.1, R11.2, SW1.2, U5.13
/riscSCK: J9.11, U1.31
/riscSCL: J10.11, U1.40
/riscSDA: J10.12, U1.37
/riscTX: J9.15, U1.39, U5.20
/sharedSCL: R6.2, U1.26, U5.12
/sharedSDA: R7.2, U1.25, U5.11
GND: C2.2, C3.2, C4.2, C6.1, C8.2, C9.1, C10.1, C11.1, C12.1, C13.2, C14.2, C16.2, C18.1, C19.2, C20.2, J1.5, J1.6, J2.2, J7.3, J7.5, J8.3, J8.5, J9.4, J9.16, R8.2, R9.2, SW1.1, U1.49, U2.4, U3.2, U4.2, U5.10, U5.28, U6.2, Y1.2, Y1.4
unnamed: C2.1, U1.9, Y1.1
unnamed: C3.1, U1.10, Y1.3
unnamed: C5.1, C7.1, U1.8
unnamed: C5.2, C7.2, R1.1, U1.7
unnamed: D2.1, R5.1
unnamed: D3.1, R8.1
unnamed: D4.2, R3.2, U1.24
unnamed: R2.1, U1.18
unnamed: R9.1, U6.5

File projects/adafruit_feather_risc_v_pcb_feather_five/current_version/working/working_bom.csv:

"Id";"Designator";"Footprint";"Quantity";"Designation";"Supplier and ref";
1;"U1";"QFN-48-1EP_7x7mm_Pitch0.5mm";1;"E310-G000";;;
2;"U2";"SOIC-8";1;"IS25LPXXX";;;
3;"U5";"QFN-32-1EP_5x5mm_Pitch0.5mm";1;"SAMD21E";;;
4;"D1";"D_SOD-123";1;"MBR120";;;
5;"J2";"JST_PH_S2B-PH-SM4-TB_02x2.00mm_Angled";1;"CONN_01X02";;;
6;"J1";"Mini-USB-B-OshPark";1;"USB_OTG";;;
7;"J6,J5,J4,J3";"MountingHole_2.7mm_M2.5";4;"CONN_01X01";;;
8;"R8,R5,R10";"R_0603";3;"1k";;;
9;"R4,R3,R2,R11";"R_0603";4;"100k";;;
10;"R1";"R_0603";1;"100";;;
11;"Y1";"Crystal_SMD_TXC_7M-4pin_3.2x2.5mm";1;"Crystal_GND24_Small";;;
12;"C20,C19,C16,C14,C4";"C_0603";5;"10uF";;;
13;"C18";"C_0603";1;"1uF";;;
14;"C13,C12,C11,C10,C9,C8,C7,C6,C5";"C_0603";9;".1uF";;;
15;"C3,C2";"C_0603";2;"12pF";;;
16;"D2";"D_0603";1;"Yellow";;;
17;"D3";"D_0603";1;"Red";;;
18;"R7,R6";"R_0603";2;"4.7k";;;
19;"U6";"SOT-23-5";1;"MCP73831";;;
20;"U4";"SOT-23-5";1;"SPX3819M5-L-1-8/TR";;;
21;"U3";"SOT-23-5";1;"SPX3819M5-L-3-3/TR";;;
22;"SW1";"SW_SPST_KMR2";1;"SW_Push";;;
23;"R9";"R_0805";1;"10k";;;
24;"D4";"D_SOT-23_ANK";1;"D_Small";;;
25;"J9";"Pin_Header_Straight_1x16_Pitch2.54mm";1;"FeatherBottom";;;
26;"J10";"Pin_Header_Straight_1x12_Pitch2.54mm";1;"FeatherTop";;;
27;"J8,J7";"Pin_Header_Straight_2x05_Pitch1.27mm_SMD";2;"CONN_02X05";;;

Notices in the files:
projects/adafruit_microsd_breakout_board_microsd/current_version/working/working.kicad_pcb:
CC BY-SA
